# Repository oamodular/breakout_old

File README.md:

# Breakout

A conduit from the USB on the rear of a module to the face of your modular setup. Breakout has a USB-A port on the rear that is routed to either the USB-A or USB-C port on the front. The rear also has three-pin connector for I2C that is exposed with a mini-TRS socket on the front.

Between you me and the sea, we designed this to accompany several upcoming firmware for [Uncertainty](https://oamodular.org/products/uncertainty) but realized this could be useful for lots of people. Modules like Instruo Lubadh and o_C (most versions) have USB on them that can be brought to the surface of your system.

Breakout is USB 2. USB 3 speeds are not supported.

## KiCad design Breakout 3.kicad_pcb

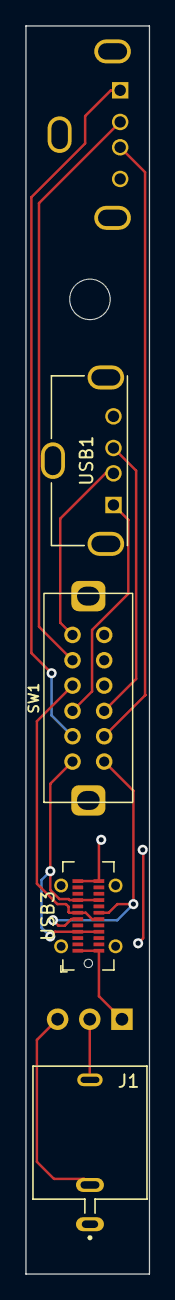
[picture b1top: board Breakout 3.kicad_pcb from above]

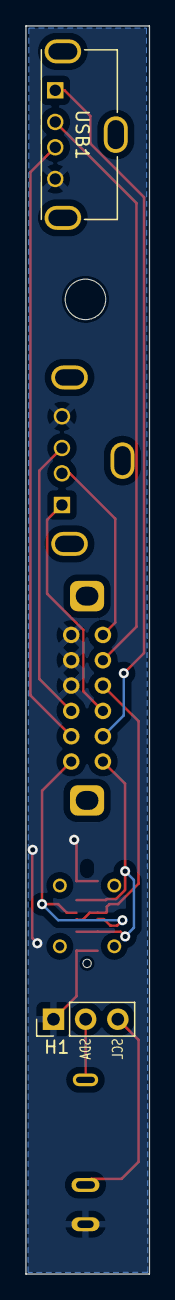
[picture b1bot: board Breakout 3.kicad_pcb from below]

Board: 2 copper layers, 9.8 x 98.6 mm, 6 parts (2 on the bottom side), 10 nets.

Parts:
H1: PinHeader_1x03_P2.54mm_Vertical
J1: THONK_PJ398SM-12; Socket-3.5mm THT-Thonkiconn PJ398SM-12
SW1: SSSF040800; Switch-4PDT Vertical THT-SSSF040800
USB1, USB1#2: USB_A_Molex_105057_Vertical
USB3: USB_C_Receptacle_GCT_USB4115-03-C

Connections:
D+: SW1.8, USB1#2.3
D+A: SW1.9, USB1.3
D+C: SW1.7, USB3.A6, USB3.B6
D-: SW1.5, USB1#2.2
D-A: SW1.6, USB1.2
D-C: SW1.4, USB3.A7, USB3.B7
Ground: H1.1, J1.1, SW1.10, SW1.11, SW1.12, USB1.4, USB1#2.4, USB3.A1, USB3.A12, USB3.B1, USB3.B12
Vcc: SW1.2, USB1#2.1
Vcc-A: SW1.3, USB1.1
Vcc-C: SW1.1, USB3.A4, USB3.A9, USB3.B4, USB3.B9

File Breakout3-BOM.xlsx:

Item # | Designator | Quantity | Manufacturer | Mfg Part # | Descripton / Value | Package / Footprint | Type | Notes
1 | J1 | 1 | Alpha/Thonk | PJ398SM-12 | Thonkiconn 3.5mm socket | THT | DNS | DO NOT INCLUDE
2 | SW1 | 1 | Alps Alpine | SSSF040800 | Slide Switch 4-pole ON-ON | THT | DNS | DO NOT INCLUDE
3 | USB3 | 1 | GCT | USB4115-03-C | USB Connectors USB C Rec 3u" vert 24p SMT & TH stakes pegs T+R+C H = 9.25 | SMD | SMD | Assemble this part only
4 | USB1, USB2 | 2 | Molex | 105057-0001 | USB Connectors FY09 VERTICAL USB A TYPE | THT | DNS | DO NOT INCLUDE
5 | H1 | 1 |  |  | 1x3 Pin Connector P2.54 | THT | DNS | DO NOT INCLUDE
6 | H2 | 1 |  |  | M3 standoff |  | DNS | DO NOT INCLUDE
7 | H3 | 1 |  |  | M3 screw |  | DNS | DO NOT INCLUDE
8 | H4 | 1 |  |  | M3 nut |  | DNS | DO NOT INCLUDE

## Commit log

2023-07-04 image for readme
2023-07-04 adding kicad assets
